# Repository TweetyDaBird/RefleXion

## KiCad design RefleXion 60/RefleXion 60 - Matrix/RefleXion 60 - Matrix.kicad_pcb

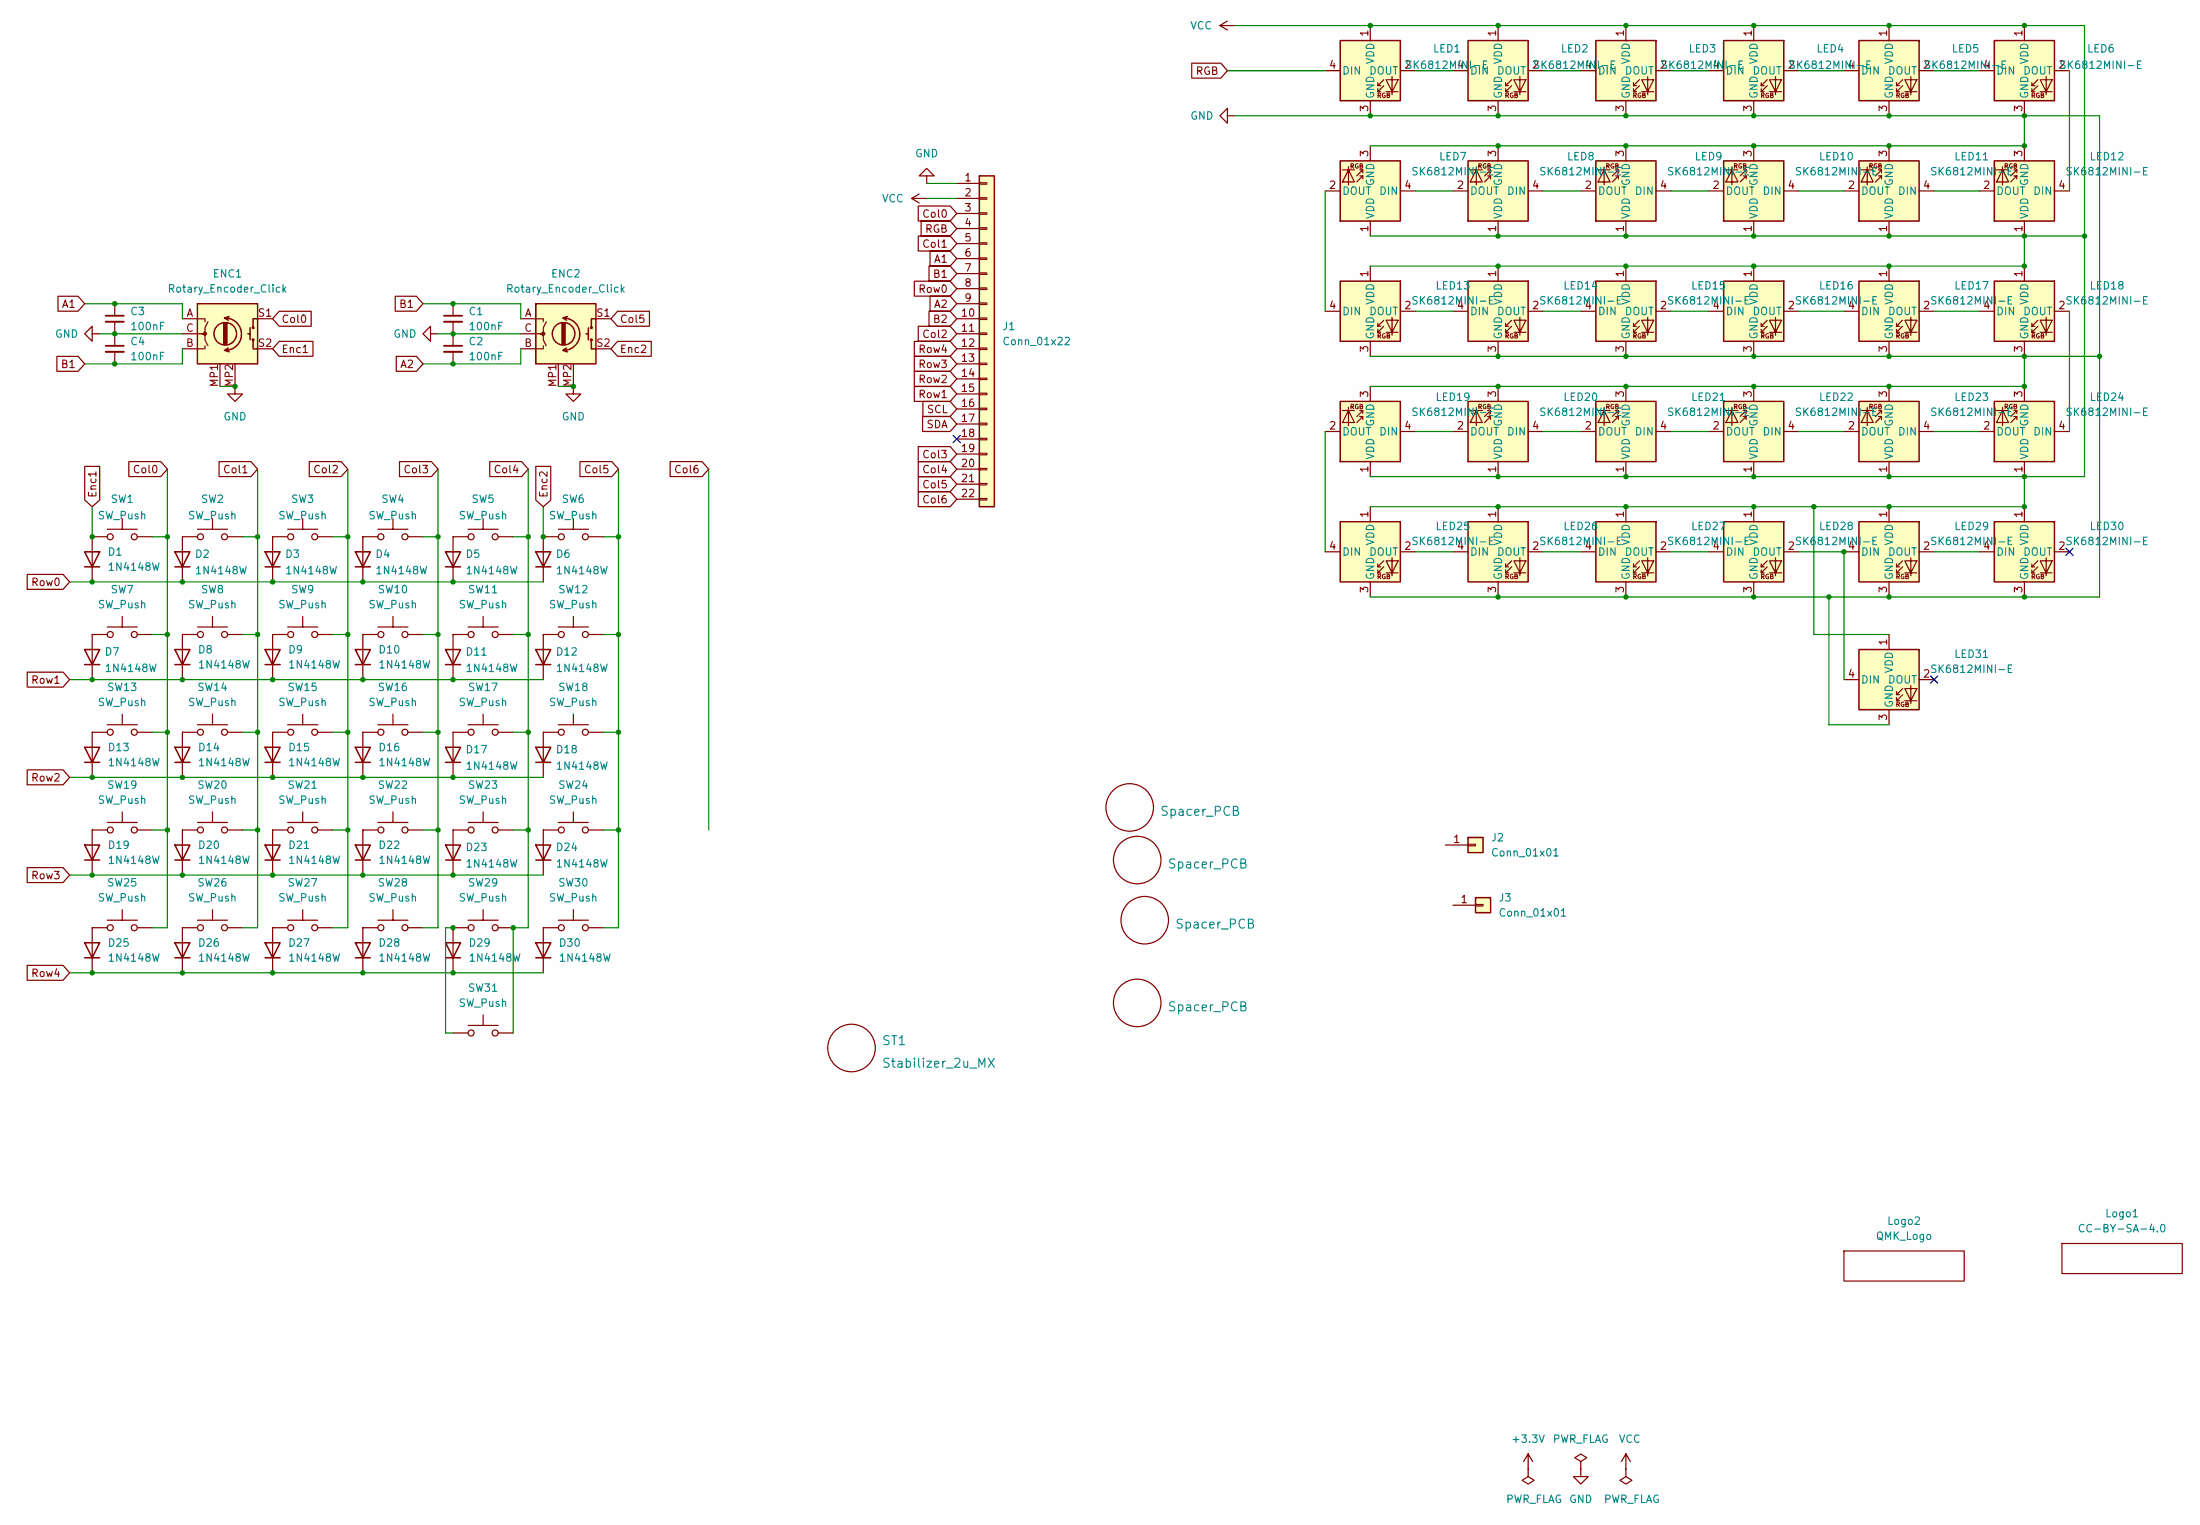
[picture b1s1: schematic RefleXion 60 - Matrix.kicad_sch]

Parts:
C1, C2, C3, C4: 100nF; C_0603_1608Metric_Pad1.08x0.95mm_HandSolder
D1, D2, D3, D4, D5, D6, D7, D8, D9, D10, D11, D12, D13, D14, D15, D16, D17, D18, D19, D20, D21, D22, D23, D24, D25, D26, D27, D28, D29, D30: 1N4148W; D_SOD-123
ENC1, ENC2: Rotary_Encoder_Click; Encoder_Alps_EC11E_Offset_pad
H1, H2, H3, H4: Spacer_PCB; Spacer PCB hole
J1: Conn_01x22; PinHeader_1x22_P2.54mm_Vertical
J2, J3: Conn_01x01; PinHeader_1x01_P2.54mm_Vertical
LED1, LED2, LED3, LED4, LED5, LED6, LED7, LED8, LED9, LED10, LED11, LED12, LED13, LED14, LED15, LED16, LED17, LED18, LED19, LED20, LED21, LED22, LED23, LED24, LED25, LED26, LED27, LED28, LED29, LED30, LED31: SK6812MINI-E; MX_SK6812MINI-E_REVERSIBLE
Logo1: CC-BY-SA-4.0; CC_BY_SA_40
Logo2: QMK_Logo; Powered_by_QMK
ST1: Stabilizer_2u_MX; Stabilizer_Cherry_MX_2.00u
SW1, SW2, SW3, SW4, SW5, SW6, SW7, SW8, SW9, SW10, SW11, SW12, SW13, SW14, SW15, SW16, SW17, SW18, SW19, SW20, SW21, SW22, SW23, SW24, SW25, SW26, SW27, SW28, SW29, SW30, SW31: SW_Push; SW_MX_HotSwap_Reversible

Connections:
A1: C3.1, ENC1.A, J1.6
A2: C2.2, ENC2.B, J1.9
B1: C1.1, C4.2, ENC1.B, ENC2.A, J1.7
B2: J1.10
Col0: ENC1.S1, J1.3, SW1.2, SW7.2, SW13.2, SW19.2, SW25.2
Col1: J1.5, SW2.2, SW8.2, SW14.2, SW20.2, SW26.2
Col2: J1.11, SW3.2, SW9.2, SW15.2, SW21.2, SW27.2
Col3: J1.19, SW4.2, SW10.2, SW16.2, SW22.2, SW28.2
Col4: J1.20, SW5.2, SW11.2, SW17.2, SW23.2, SW29.2, SW31.1
Col5: ENC2.S1, J1.21, SW6.2, SW12.2, SW18.2, SW24.2, SW30.2
Col6: J1.22
Enc1: D1.2 (A), ENC1.S2, SW1.1
Enc2: D6.2 (A), ENC2.S2, SW6.1
GND: C1.2, C2.1, C3.2, C4.1, ENC1.C, ENC1.MP1 (GND), ENC1.MP2 (GND), ENC2.C, ENC2.MP1 (GND), ENC2.MP2 (GND), J1.1, LED1.3 (GND), LED2.3 (GND), LED3.3 (GND), LED4.3 (GND), LED5.3 (GND), LED6.3 (GND), LED7.3 (GND), LED8.3 (GND), LED9.3 (GND), LED10.3 (GND), LED11.3 (GND), LED12.3 (GND), LED13.3 (GND), LED14.3 (GND), LED15.3 (GND), LED16.3 (GND), LED17.3 (GND), LED18.3 (GND), LED19.3 (GND), LED20.3 (GND), LED21.3 (GND), LED22.3 (GND), LED23.3 (GND), LED24.3 (GND), LED25.3 (GND), LED26.3 (GND), LED27.3 (GND), LED28.3 (GND), LED29.3 (GND), LED30.3 (GND), LED31.3 (GND)
unnamed: D2.2 (A), SW2.1
unnamed: D3.2 (A), SW3.1
unnamed: D4.2 (A), SW4.1
unnamed: D5.2 (A), SW5.1
unnamed: D7.2 (A), SW7.1
unnamed: D8.2 (A), SW8.1
unnamed: D9.2 (A), SW9.1
unnamed: D10.2 (A), SW10.1
unnamed: D11.2 (A), SW11.1
unnamed: D12.2 (A), SW12.1
unnamed: D13.2 (A), SW13.1
unnamed: D14.2 (A), SW14.1
unnamed: D15.2 (A), SW15.1
unnamed: D16.2 (A), SW16.1
unnamed: D17.2 (A), SW17.1
unnamed: D18.2 (A), SW18.1
unnamed: D19.2 (A), SW19.1
unnamed: D20.2 (A), SW20.1
unnamed: D21.2 (A), SW21.1
unnamed: D22.2 (A), SW22.1
unnamed: D23.2 (A), SW23.1
unnamed: D24.2 (A), SW24.1
unnamed: D25.2 (A), SW25.1
unnamed: D26.2 (A), SW26.1
unnamed: D27.2 (A), SW27.1
unnamed: D28.2 (A), SW28.1
unnamed: D29.2 (A), SW29.1, SW31.2
unnamed: D30.2 (A), SW30.1
unnamed: LED1.2 (DOUT), LED2.4 (DIN)
unnamed: LED2.2 (DOUT), LED3.4 (DIN)
unnamed: LED3.2 (DOUT), LED4.4 (DIN)
unnamed: LED4.2 (DOUT), LED5.4 (DIN)
unnamed: LED5.2 (DOUT), LED6.4 (DIN)
unnamed: LED7.4 (DIN), LED8.2 (DOUT)
unnamed: LED8.4 (DIN), LED9.2 (DOUT)
unnamed: LED9.4 (DIN), LED10.2 (DOUT)
unnamed: LED10.4 (DIN), LED11.2 (DOUT)
unnamed: LED11.4 (DIN), LED12.2 (DOUT)
unnamed: LED6.2 (DOUT), LED12.4 (DIN)
unnamed: LED13.2 (DOUT), LED14.4 (DIN)
unnamed: LED7.2 (DOUT), LED13.4 (DIN)
unnamed: LED14.2 (DOUT), LED15.4 (DIN)
unnamed: LED15.2 (DOUT), LED16.4 (DIN)
unnamed: LED16.2 (DOUT), LED17.4 (DIN)
unnamed: LED17.2 (DOUT), LED18.4 (DIN)
unnamed: LED18.2 (DOUT), LED24.4 (DIN)
unnamed: LED19.2 (DOUT), LED25.4 (DIN)
unnamed: LED19.4 (DIN), LED20.2 (DOUT)
unnamed: LED20.4 (DIN), LED21.2 (DOUT)
unnamed: LED21.4 (DIN), LED22.2 (DOUT)
unnamed: LED22.4 (DIN), LED23.2 (DOUT)
unnamed: LED23.4 (DIN), LED24.2 (DOUT)
unnamed: LED25.2 (DOUT), LED26.4 (DIN)
unnamed: LED26.2 (DOUT), LED27.4 (DIN)
unnamed: LED27.2 (DOUT), LED28.4 (DIN)
unnamed: LED29.2 (DOUT), LED30.4 (DIN)
unnamed: LED28.2 (DOUT), LED29.4 (DIN), LED31.4 (DIN)
RGB: J1.4, LED1.4 (DIN)
Row0: D1.1 (K), D2.1 (K), D3.1 (K), D4.1 (K), D5.1 (K), D6.1 (K), J1.8
Row1: D7.1 (K), D8.1 (K), D9.1 (K), D10.1 (K), D11.1 (K), D12.1 (K), J1.15
Row2: D13.1 (K), D14.1 (K), D15.1 (K), D16.1 (K), D17.1 (K), D18.1 (K), J1.14
Row3: D19.1 (K), D20.1 (K), D21.1 (K), D22.1 (K), D23.1 (K), D24.1 (K), J1.13
Row4: D25.1 (K), D26.1 (K), D27.1 (K), D28.1 (K), D29.1 (K), D30.1 (K), J1.12
SCL: J1.16
SDA: J1.17
VCC: J1.2, LED1.1 (VDD), LED2.1 (VDD), LED3.1 (VDD), LED4.1 (VDD), LED5.1 (VDD), LED6.1 (VDD), LED7.1 (VDD), LED8.1 (VDD), LED9.1 (VDD), LED10.1 (VDD), LED11.1 (VDD), LED12.1 (VDD), LED13.1 (VDD), LED14.1 (VDD), LED15.1 (VDD), LED16.1 (VDD), LED17.1 (VDD), LED18.1 (VDD), LED19.1 (VDD), LED20.1 (VDD), LED21.1 (VDD), LED22.1 (VDD), LED23.1 (VDD), LED24.1 (VDD), LED25.1 (VDD), LED26.1 (VDD), LED27.1 (VDD), LED28.1 (VDD), LED29.1 (VDD), LED30.1 (VDD), LED31.1 (VDD)

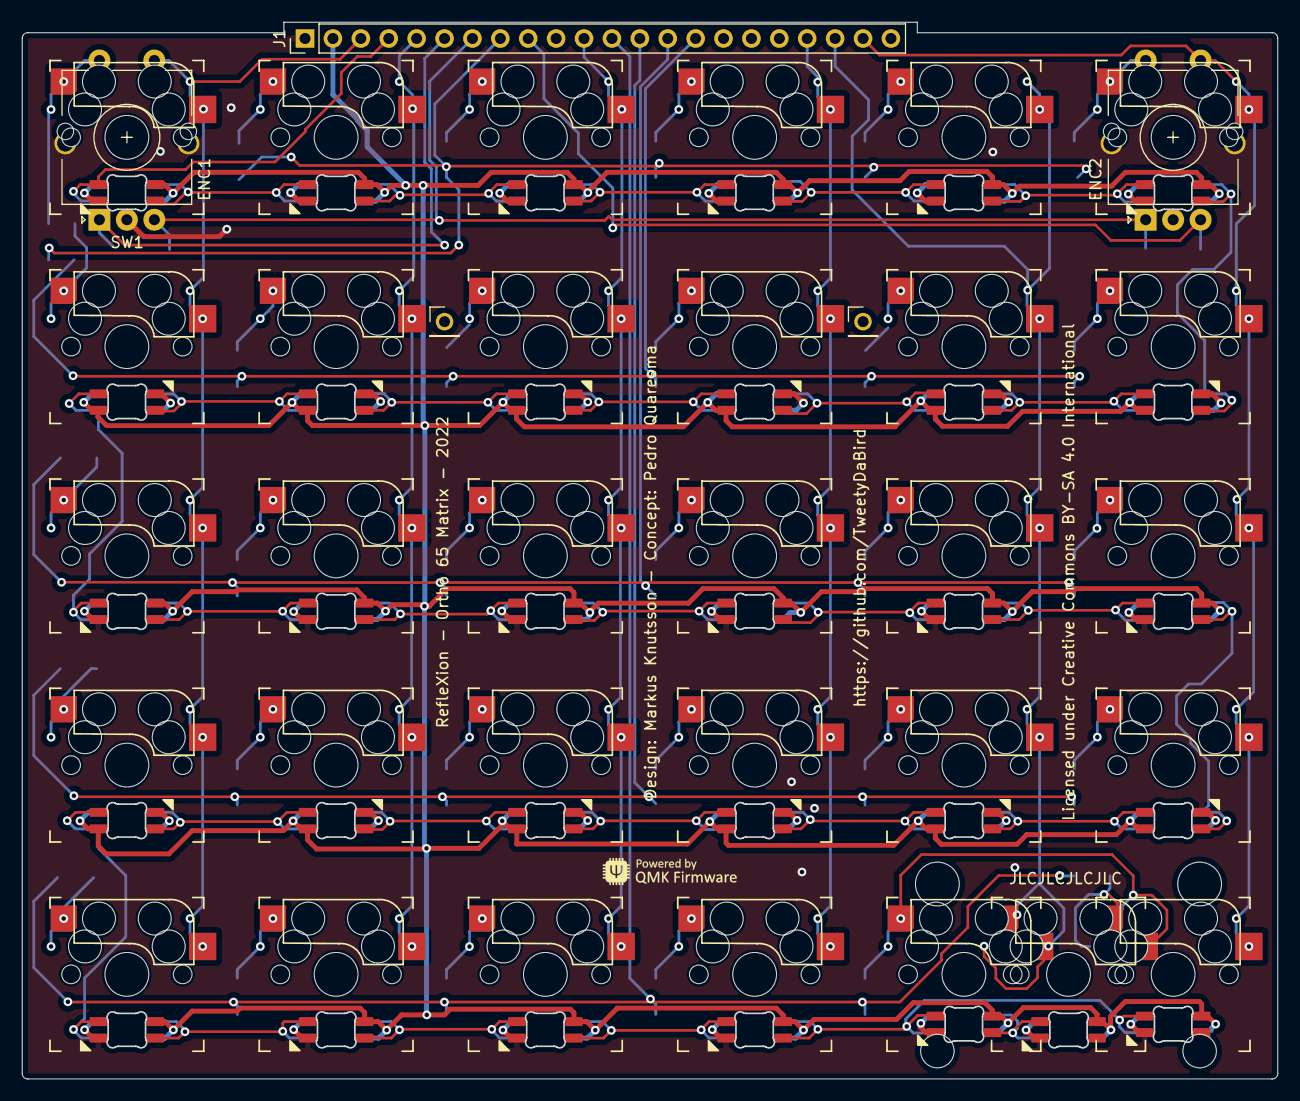
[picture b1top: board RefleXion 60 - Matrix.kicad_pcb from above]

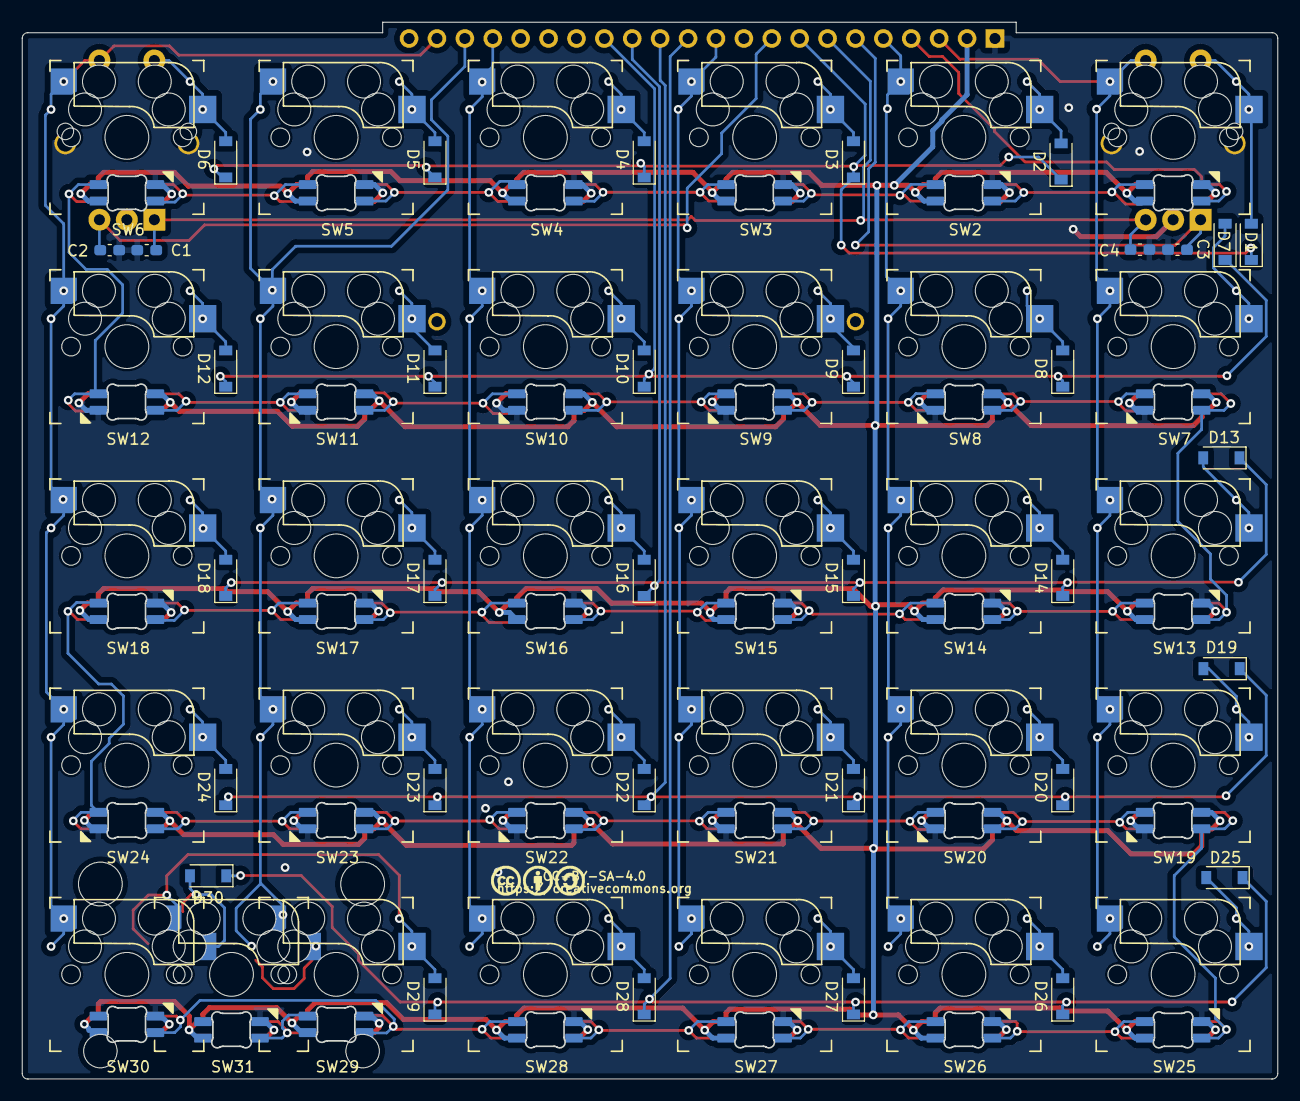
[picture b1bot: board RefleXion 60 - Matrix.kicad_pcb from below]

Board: 2 copper layers, 114.3 x 96.2 mm, 108 parts (35 on the bottom side), 76 nets.

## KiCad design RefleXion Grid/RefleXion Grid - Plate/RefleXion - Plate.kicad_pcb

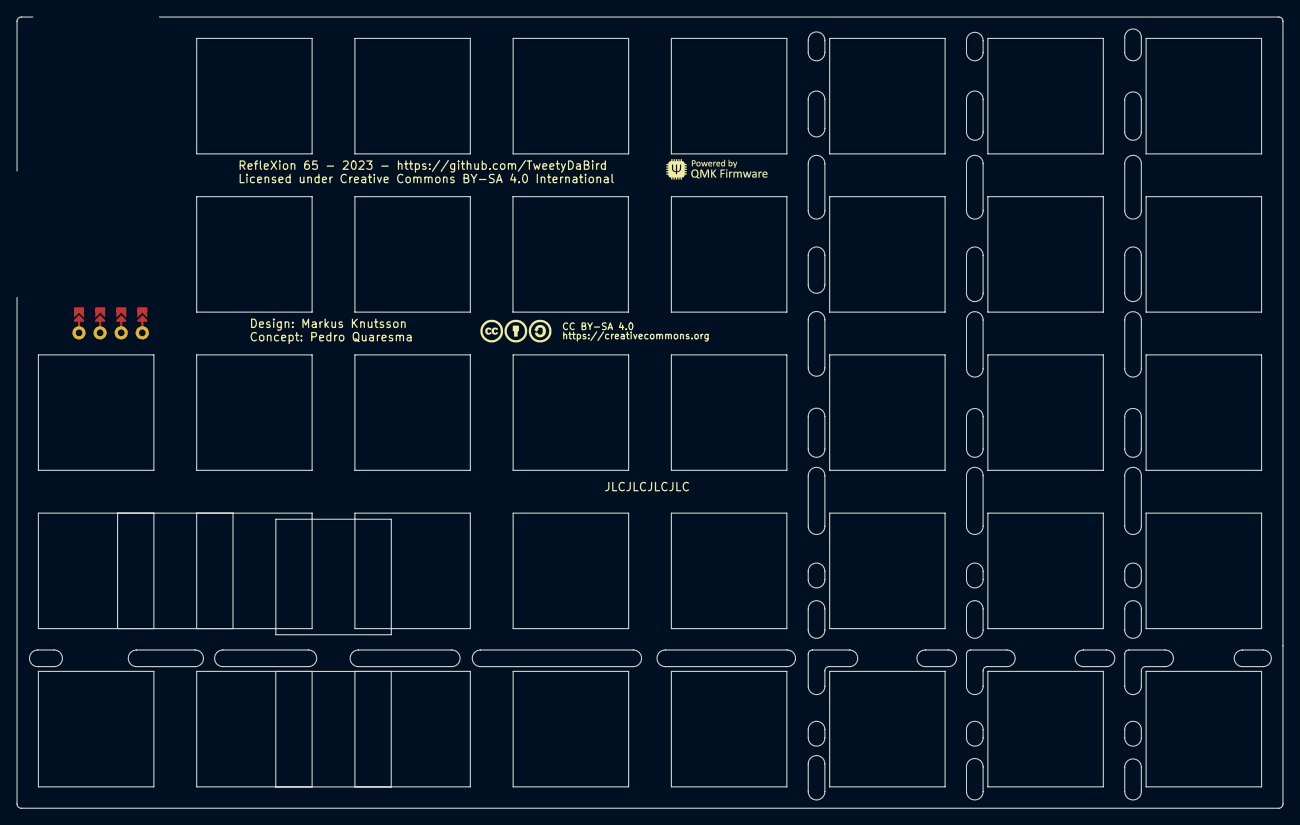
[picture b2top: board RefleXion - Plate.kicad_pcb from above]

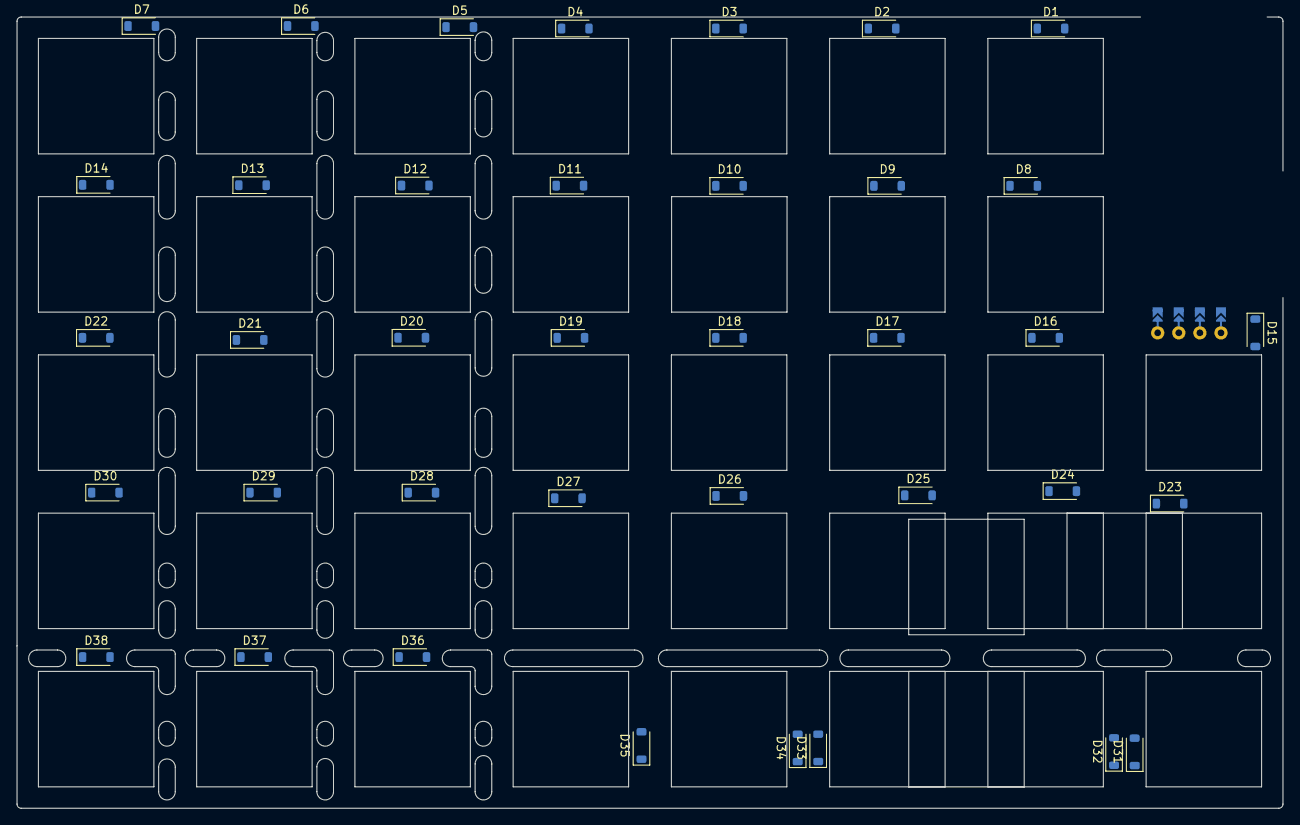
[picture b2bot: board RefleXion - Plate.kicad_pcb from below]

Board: 2 copper layers, 152.4 x 95.2 mm, 85 parts (38 on the bottom side), 5 nets, no tracks yet.

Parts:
D1, D2, D3, D4, D5, D6, D7, D8, D9, D10, D11, D12, D13, D14, D15, D16, D17, D18, D19, D20, D21, D22, D23, D24, D25, D26, D27, D28, D29, D30, D31, D32, D33, D34, D35, D36, D37, D38: 1N4148W; D_SOD-123
Logo1: CC-BY-SA-4.0; CC_BY_SA_40_line
Logo2: QMK_Logo; Powered_by_QMK
OLED1: OLED_4pin; SSD1306-0.91-OLED-4pin-128x32 doublesided
ST1, ST2, ST3: Stabilizer_2u_MX; Stabilizer_Cherry_MX_2.00u
SW1, SW2, SW3, SW4, SW5, SW6, SW7, SW8, SW9, SW10, SW11, SW12, SW13, SW14, SW15, SW16, SW17, SW18, SW19, SW20, SW21, SW22, SW23, SW24, SW25, SW26, SW27, SW28, SW29, SW30, SW31, SW32, SW33, SW34, SW35, SW36, SW37, SW38, SW39, SW40, SW41: SW_Push; SW_MX_Plate_Placeholder_nodrill_NOBORDER_13,9

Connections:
Row0: D1.1 (K), D2.1 (K), D3.1 (K), D4.1 (K), D5.1 (K), D6.1 (K), D7.1 (K)
Row1: D8.1 (K), D9.1 (K), D10.1 (K), D11.1 (K), D12.1 (K), D13.1 (K), D14.1 (K)
Row2: D15.1 (K), D16.1 (K), D17.1 (K), D18.1 (K), D19.1 (K), D20.1 (K), D21.1 (K), D22.1 (K)
Row3: D23.1 (K), D24.1 (K), D25.1 (K), D26.1 (K), D27.1 (K), D28.1 (K), D29.1 (K), D30.1 (K)
Row4: D31.1 (K), D32.1 (K), D33.1 (K), D34.1 (K), D35.1 (K), D36.1 (K), D37.1 (K), D38.1 (K)

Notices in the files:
RefleXion 60/RefleXion 60 - Matrix/RefleXion 60 - Matrix.kicad_pcb:
Licensed under Creative Commons BY-SA 4.0 International
